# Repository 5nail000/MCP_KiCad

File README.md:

# KiCad AI — локальная среда Cursor → MCP → KiCad

## 1. What is this?

Рабочая среда для **AI-assisted engineering** в KiCad: LLM через MCP создаёт и правит **настоящие** `.kicad_sch` / `.kicad_pro`, проверяет связность, гоняет ERC/DRC и BOM через официальный `kicad-cli`. SKiDL — опциональный Python-слой; KiCad остаётся источником истины.

Это не генератор картинок и не mock. Схему можно открыть в KiCad 10.

## 2. Architecture

```
Cursor Agent  --stdio MCP-->  kicad-ai (whitelist + backup + logs)
                                |                         |
                                v                         v
                         kicad-sch-api 0.5.6          kicad-cli 10.0.6
                                |                     ERC / DRC / netlist
                                +-----> projects/**  (source of truth)

                         SKiDL 2.3.0  --> skidl_lab/  (blocks, tests, generated netlists)
                                          never overwrites projects/*.kicad_sch
```

- Schematic engine: пакет [`kicad-sch-api`](https://pypi.org/project/kicad-sch-api/) (реальный S-expression parser/writer).
- ERC / DRC / BOM / netlist / `sch upgrade`: `C:\Program Files\KiCad\10.0\bin\kicad-cli.exe`.
- SKiDL 2.3.0 (`KICAD10`): блоки и Python ERC в `skidl_lab/` (не пакетный каталог `skidl/`, чтобы не перекрыть PyPI).
- Stock `kicad-sch-mcp` **не** подключён напрямую: у него нет whitelist путей.

Отклонённые альтернативы и будущие слои: [docs/architecture.md](docs/architecture.md).

## 3. Requirements

Проверено на этой машине:

- Windows 10 x64
- KiCad **10.0.6** (`C:\Program Files\KiCad\10.0\`)
- Python **3.12** через uv (системный 3.14 не используется)
- uv 0.12.x
- Git

## 4. Installation

В PowerShell из корня репозитория:

```powershell
cd C:\Cursor_Projects\MCP_KiCad
.\scripts\setup.ps1
```

Эквивалент вручную:

```powershell
uv sync --group dev
uv run doctor
```

## 5. Configuration

Скопируйте `.env.example` в `.env` только если автоопределение KiCad не сработало.

Переменные:

- `KICAD_AI_WORKSPACE` — корень workspace (Cursor задаёт сам)
- `KICAD_EXE`, `KICAD_CLI`, `KICAD_SYMBOL_DIR`, `KICAD_FOOTPRINT_DIR` — ручные пути
- `KICAD_AI_BACKUP_KEEP` — сколько backup хранить (по умолчанию 10)
- `KICAD_AI_LOG_LEVEL` — `INFO` / `DEBUG`

## 6. Cursor MCP setup

Файл [`.cursor/mcp.json`](.cursor/mcp.json) запускает `.venv/Scripts/python.exe -m kicad_ai.mcp.server` (быстрее и совместимо с Cursor; MCP 1.x).

1. Откройте этот folder как workspace Cursor.
2. Cursor Settings → MCP → включите сервер `kicad`.
3. Подтвердите tools.
4. Проверка: `uv run doctor` должен показать `[OK] MCP configuration`.

Ручной запуск (обычно не нужен):

```powershell
uv run start-mcp
.\scripts\start-mcp.ps1
```

## 7. Creating first project

Скажите агенту:

> Создай проект контроллера насоса в projects/user/pump-controller

Агент должен вызвать `create_project`, затем добавлять символы из библиотек KiCad, соединять пины, сохранить, прогнать ERC.

Пример из репозитория:

```powershell
uv run kicad-ai example
```

создаёт `projects/examples/mcp-test/` (12V → предохранитель → R-78E5.0-0.5 → 5V + LED). Рядом лежит тестовая плата `mcp-test.kicad_pcb` (не для производства). `kicad-ai example` с overwrite перезапишет каталог, после этого плату нужно собрать снова скриптом из §11.

## 8. Working with existing projects

1. `list_projects` / `load_schematic`
2. `get_schematic_info` + `inspect_connectivity`
3. Предложить изменение
4. `save_schematic` (backup создаётся автоматически)
5. `validate_project` (ERC + DRC; нет PCB → DRC SKIPPED)
6. Показать summary

Проекты пользователя кладите в `projects/user/`. Каталог `projects/` в `.gitignore` — схемы и платы не попадают в git, только локально. Не пишите вне workspace: MCP это запретит.

## 9. Backup and rollback

Перед перезаписью существующей схемы MCP копирует проект в `backups/<name>/YYYY-MM-DD_HHMMSS/`. Старые копии чистятся (последние 10).

```powershell
.\scripts\backup-project.ps1 projects\examples\mcp-test
uv run kicad-ai backup projects\examples\mcp-test
```

Откат: tool `restore_backup` или копирование папки backup обратно в project dir.

## 10. Validation

```powershell
uv run doctor
uv run kicad-ai validate projects\examples\mcp-test
uv run pytest -v
.\scripts\open-kicad.ps1
```

Doctor проверяет KiCad, Python 3.12, uv, Git, kicad-sch-api, SKiDL, `.cursor/mcp.json`, workspace.

`validate` гоняет настоящий `kicad-cli sch erc` и `kicad-cli pcb drc`. Если `.kicad_pcb` нет, DRC = SKIPPED (не PASS).

Python-тесты: `tests/test_electrical.py` (KiCad ERC/DRC/netlist) и `skidl_lab/tests/` (SKiDL ERC). SKiDL не пишет схему проекта.

## 11. PCB

MCP **не создаёт** `.kicad_pcb`: ни автоматически после схемы, ни по запросу из Cursor. `create_project` пишет только `.kicad_pro` + `.kicad_sch`. Tool `run_drc` / `validate_project` при отсутствии платы возвращают **SKIPPED** (это не PASS и не проверка разводки).

У примеров уже есть **тестовые** платы (smoke для DRC и 2D/3D render, не Gerber). Пересборка только через pcbnew KiCad 10:

```powershell
& "C:\Program Files\KiCad\10.0\bin\python.exe" scripts\build_mcp_test_pcb.py
uv run kicad-ai validate projects\examples\mcp-test

& "C:\Program Files\KiCad\10.0\bin\python.exe" scripts\build_oxy_pcb.py
uv run kicad-ai validate projects\oxy\oxy
uv run kicad-ai render-pcb projects\oxy\oxy
uv run kicad-ai render-3d projects\oxy\oxy
```

`mcp-test`: F1, U1, R1, D1, 40×26 мм. `oxy`: F1, J1/J2 (XH2.54), R1, D1, 55×30 мм, GND/GNDA разведены.

Готовую к производству плату MCP не соберёт. Нормальный путь для своих проектов — KiCad GUI:

```powershell
uv run kicad-ai open projects\examples\mcp-test\mcp-test.kicad_pro
```

1. PCB Editor (если файла платы нет, KiCad создаст пустой `*.kicad_pcb`).
2. **Update PCB from Schematic** (`F8`) — футпринты и нетлист со схемы, не разводка.
3. Контур, расстановка, дорожки, полигоны, крепёж — руками в pcbnew.
4. DRC в PCB Editor, затем снова `uv run kicad-ai validate …` (DRC уже не SKIPPED).

`Update PCB from Schematic` — не «плата на печать». Gerber / drill / Pick & Place в этой среде **не реализованы**. Не просите агента имитировать их.

## 12. skidl_lab

[`skidl_lab/`](skidl_lab/README.md) — опциональный Python-слой на SKiDL 2.3.0 (`KICAD10`). Каталог назван `skidl_lab`, а не `skidl`: имя `skidl` занято пакетом PyPI (`import skidl` vs `import skidl_lab`).

KiCad-файлы в `projects/` остаются источником истины. SKiDL **не** перезаписывает `.kicad_sch` / `.kicad_pcb` / `.kicad_pro`. Нетлисты только в `skidl_lab/generated/`.

| Путь | Назначение |
|---|---|
| `skidl_lab/blocks/` | Переиспользуемые блоки (`led_indicator`, `rail_12v_5v`) |
| `skidl_lab/circuits/` | Сборки из блоков; `mcp_test_equivalent` повторяет *архитектуру* примера, но не заменяет `projects/examples/mcp-test` |
| `skidl_lab/tests/` | SKiDL ERC в pytest |
| `skidl_lab/generated/` | Артефакты (gitignore), не схема проекта |

MCP: `list_skidl_blocks`, `run_skidl_erc`, `export_skidl_netlist` (отказ, если путь в `projects/` или расширение `.kicad_sch`).

```powershell
uv run kicad-ai skidl-erc led_indicator
uv run kicad-ai skidl-erc rail_12v_5v
```

## 13. Visualization

Картинки строятся из `.kicad_sch` / `.kicad_pcb` через **kicad-cli**, не через AI/Blender/скриншот.

```powershell
uv run python scripts/render_project.py projects\examples\mcp-test
uv run kicad-ai render-schematic projects\examples\mcp-test
uv run kicad-ai render-pcb projects\examples\mcp-test
uv run kicad-ai render-3d projects\examples\mcp-test
```

Выход (gitignore): `renders/<project>/schematic|pcb|3d/` и `renders/render_report.json`.

| Запрос | Tool | Движок |
|---|---|---|
| Покажи схему | `render_schematic` | `kicad-cli sch export svg/pdf` → PNG |
| Покажи плату | `render_pcb` | `kicad-cli pcb export svg` |
| Плата в 3D | `render_pcb_3d` | `kicad-cli pcb render` |
| Весь проект | `render_project` | всё доступное; нет PCB → SKIPPED |

Темы `light` / `dark` (dark — presentation invert чёрной туши, геометрия та же). Виды схемы: `full` и имена из [`render.yaml`](render.yaml) (`power`, `indicator`, …) — SKIPPED, если на листе нет указанных reference. DPI: preview 150 / docs 300 / large 600. Кадрирование SVG по bounding box + `render.margin` в миллиметрах (по умолчанию 15, чтобы не резать labels и не оставлять пустой лист).

Авторендер после validation выключен (`automation.render_after_validation: false`). Устаревший PNG не показывается: `*.meta.json` хранит `source_hash`, при изменении схемы рендер пересобирается.

Нет `.kicad_pcb` — PCB/3D не симулируются. 3D-модели отсутствуют → WARNING, пайплайн продолжается.

## 14. Troubleshooting

См. [docs/troubleshooting.md](docs/troubleshooting.md). Логи: `logs/kicad-ai-YYYYMMDD.log` (каждая строка начинается с времени). Traceback не скрывается.

## 15. Example prompts for LLM

1. Создай проект `projects/user/pump-controller` с входом 12V, предохранителем и DC-DC 5V.
2. Прочитай `projects/examples/mcp-test` и перечисли компоненты и цепи.
3. Добавь в mcp-test конденсатор 100nF на выход 5V, сохрани backup и покажи connectivity.
4. Найди в библиотеках KiCad символ предохранителя, не создавай новый.
5. Соедини выход U1 с net `VOUT_5V` через label, не считая пересечение проводов соединением.
6. Прогони `validate_project` по текущей схеме, объясни ERC и статус DRC (PASS/FAIL/SKIPPED).
7. Сгенерируй BOM CSV для mcp-test.
8. Добавь защиту от обратной полярности (диод) на вход 12V, не меняя существующие reference.
9. Покажи dangling pins и неподключённые power pins.
10. Сделай backup mcp-test, затем откати последнее изменение.
11. Прогони SKiDL ERC для блока `led_indicator`; не пиши из SKiDL в `projects/`.
12. Плату проекта не генерируй через MCP. Для mcp-test тестовый `.kicad_pcb` уже есть; для своих плат — KiCad GUI и Update PCB from Schematic.
13. Покажи схему mcp-test (`render_schematic`), не генерируй картинку нейросетью.
14. Покажи плату mcp-test в 2D и 3D (`render_pcb`, `render_pcb_3d`). Если у проекта нет `.kicad_pcb` — SKIPPED, без фейковой картинки.

Команды Windows:

```powershell
uv sync
uv run doctor
uv run start-mcp
uv run pytest -v
uv run kicad-ai example
uv run kicad-ai validate projects\examples\mcp-test
uv run kicad-ai skidl-erc led_indicator
uv run python scripts/render_project.py projects\examples\mcp-test
uv run kicad-ai open projects\examples\mcp-test\mcp-test.kicad_pro
```

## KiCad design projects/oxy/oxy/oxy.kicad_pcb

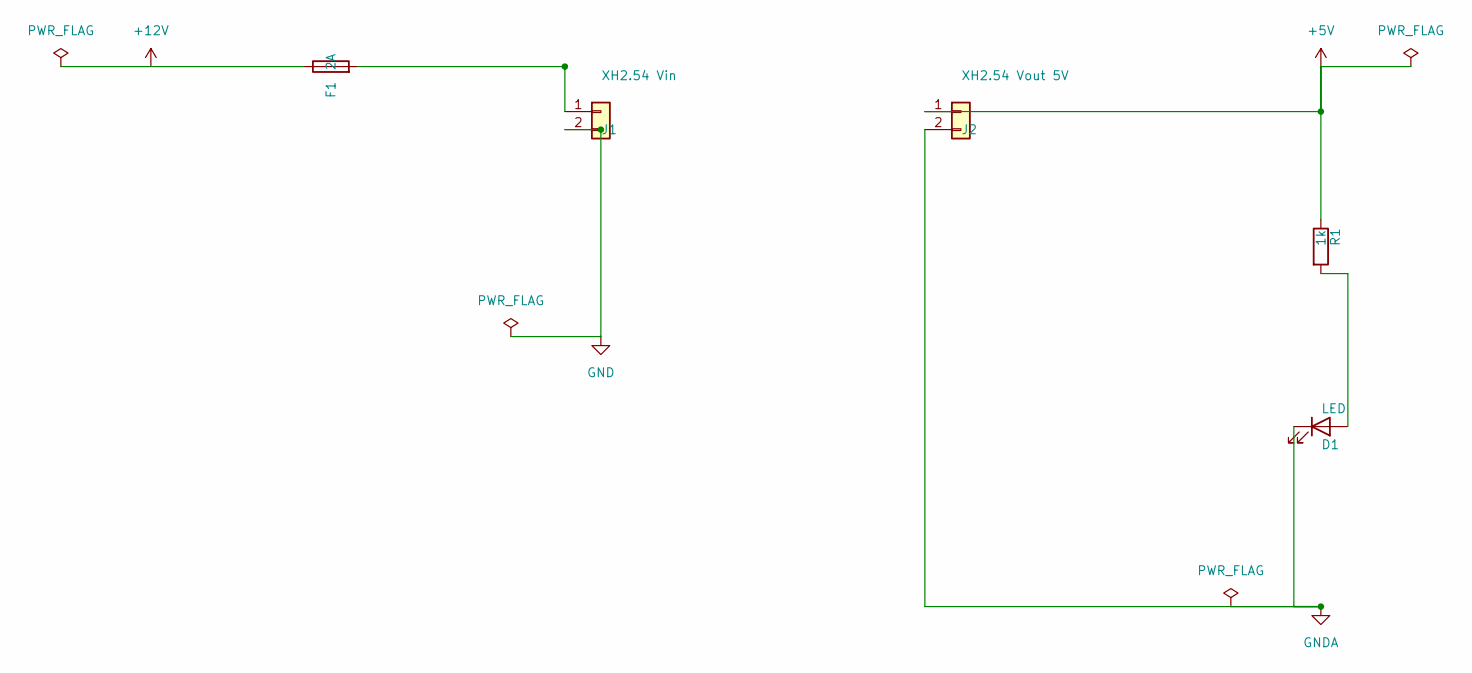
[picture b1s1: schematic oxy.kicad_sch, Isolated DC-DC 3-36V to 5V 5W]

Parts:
D1: LED; LED_0603_1608Metric
F1: 2A; Fuse_0603_1608Metric
J1: XH2.54 Vin; JST_XH_B2B-XH-A_1x02_P2.50mm_Vertical
J2: XH2.54 Vout 5V; JST_XH_B2B-XH-A_1x02_P2.50mm_Vertical
R1: 1k; R_0603_1608Metric

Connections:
+5V: J2.1, R1.1
+12V: F1.1
GND: J1.2
GNDA: D1.1 (K), J2.2
unnamed: D1.2 (A), R1.2
unnamed: F1.2, J1.1

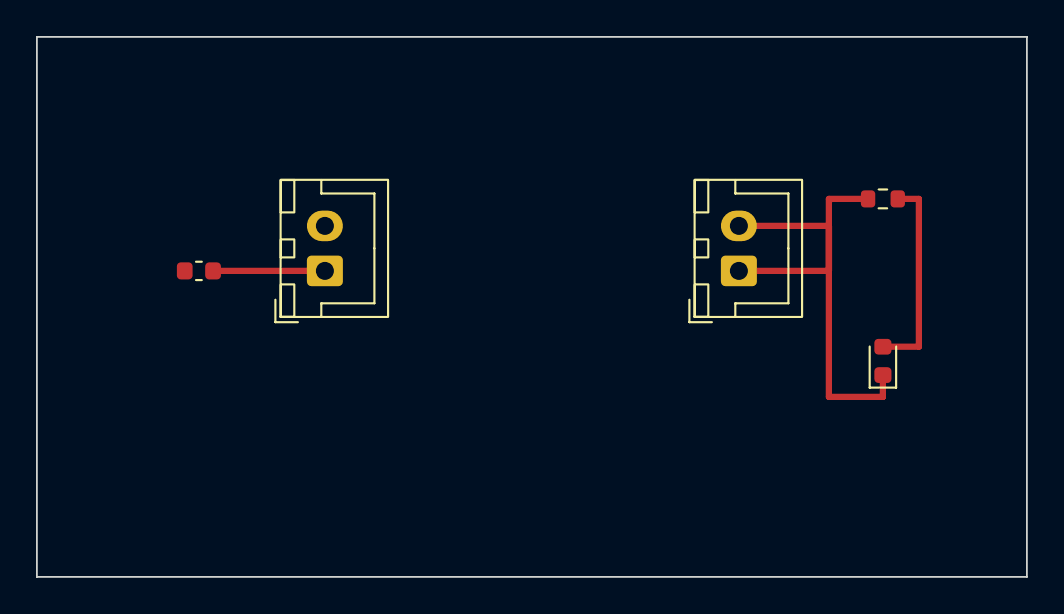
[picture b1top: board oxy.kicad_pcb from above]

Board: 2 copper layers, 55.0 x 30.0 mm, 5 parts (0 on the bottom side), 4 nets.

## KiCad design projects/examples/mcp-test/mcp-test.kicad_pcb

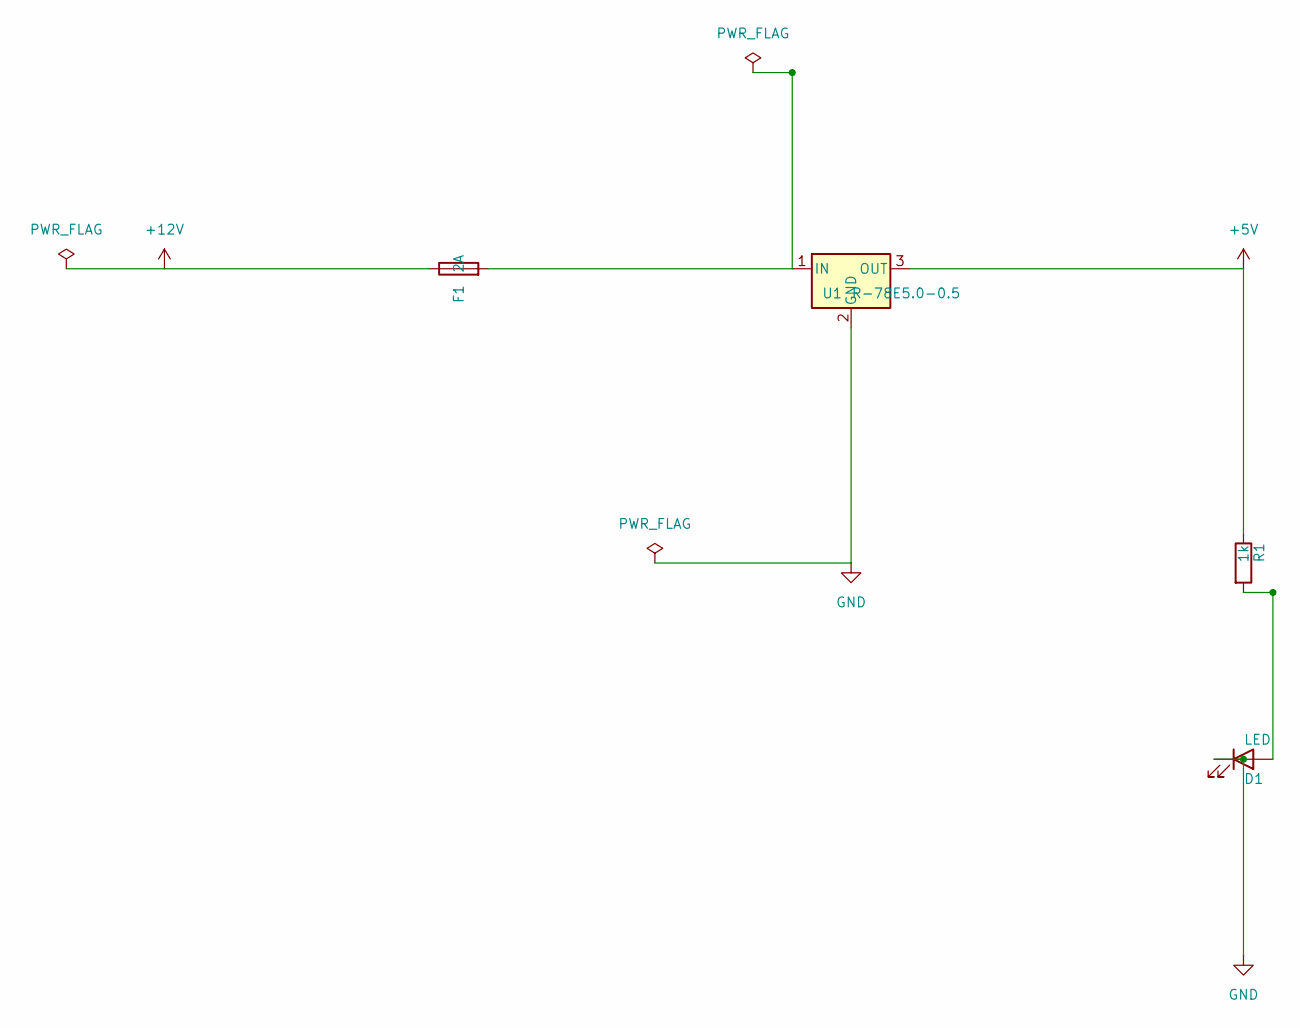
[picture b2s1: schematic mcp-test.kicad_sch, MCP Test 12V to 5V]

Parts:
D1: LED; LED_0603_1608Metric
F1: 2A; Fuse_0603_1608Metric
R1: 1k; R_0603_1608Metric
U1: R-78E5.0-0.5; Converter_DCDC_RECOM_R-78E-0.5_THT

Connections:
+5V: R1.1, U1.3 (OUT)
+12V: F1.1
GND: D1.1 (K), U1.2 (GND)
unnamed: D1.2 (A), R1.2
unnamed: F1.2, U1.1 (IN)

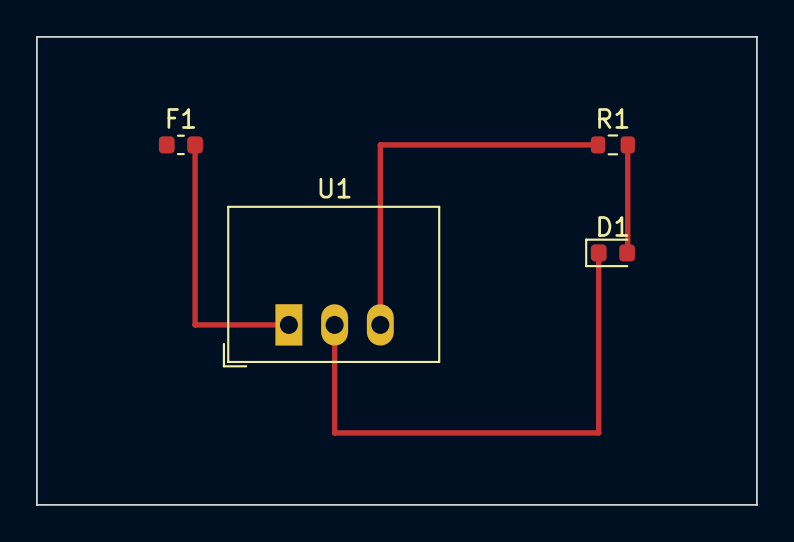
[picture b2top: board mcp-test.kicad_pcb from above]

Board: 2 copper layers, 40.0 x 26.0 mm, 4 parts (0 on the bottom side), 4 nets.
